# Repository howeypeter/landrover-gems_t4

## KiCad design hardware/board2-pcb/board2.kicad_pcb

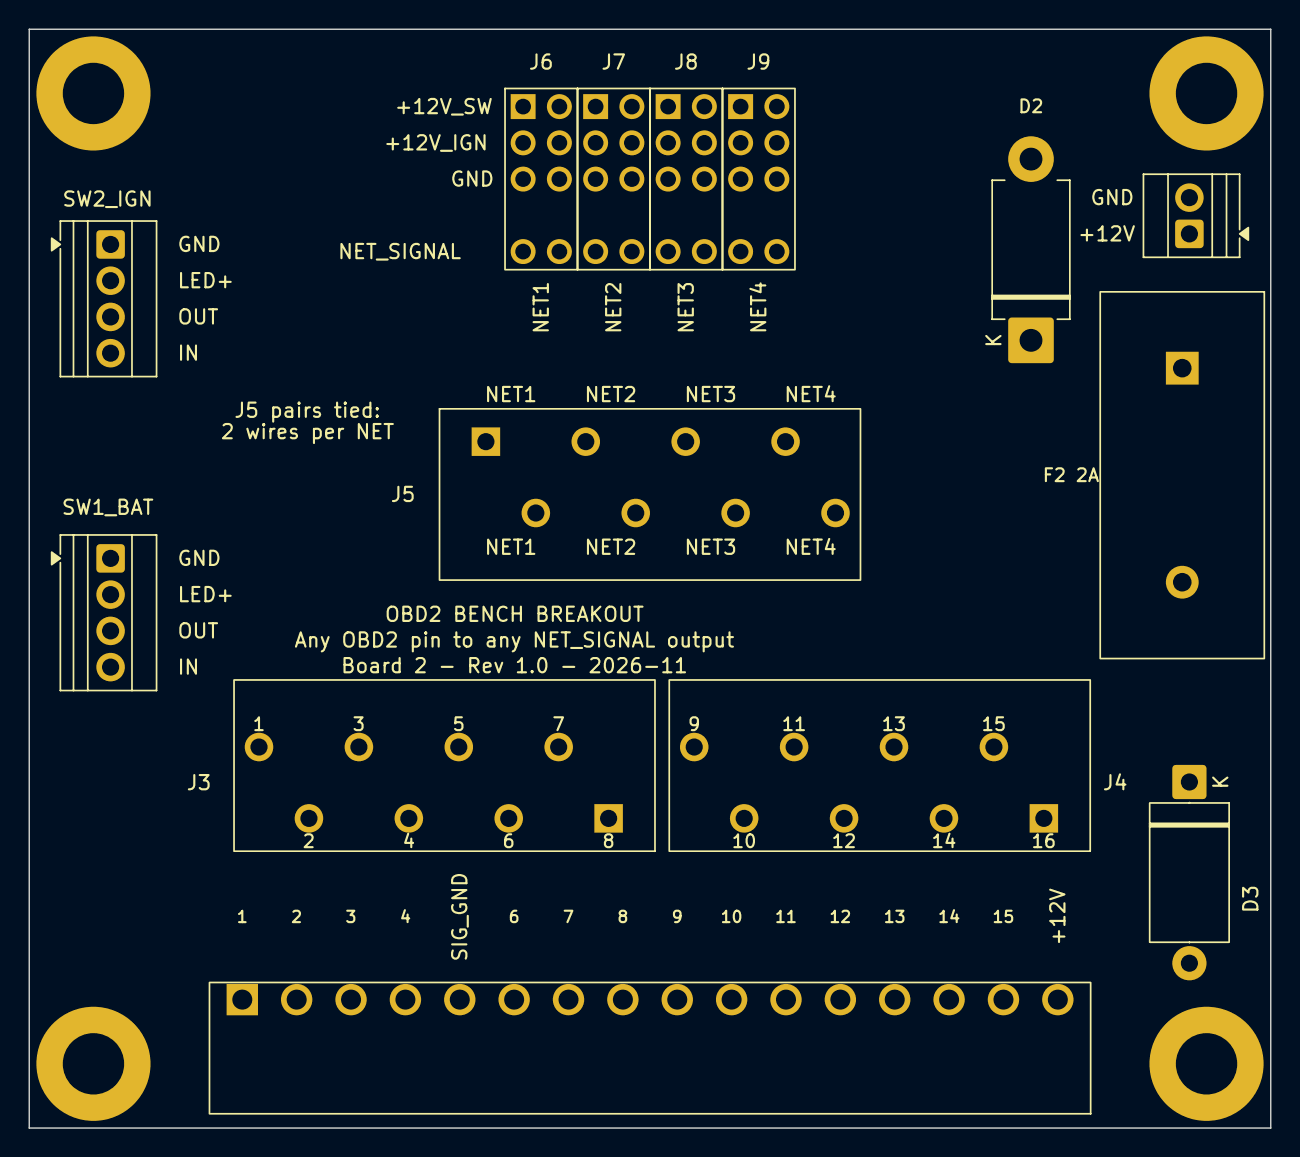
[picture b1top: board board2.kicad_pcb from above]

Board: 2 copper layers, 87.0 x 77.0 mm, 18 parts (0 on the bottom side), 24 nets, no tracks yet.

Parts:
D2: D2; D_DO-201AD_P12.70mm_Horizontal
D3: D3; D_DO-27_P12.70mm_Horizontal
F2: F2; Fuseholder_2pin_5x20_P15mm
H: MountingHole_4.3mm_M4_Pad
H#2, H#3, H#4: MountingHole_4.3mm_M4_Pad
J1: J1; TerminalBlock_Xinya_XY308-2.54-2P_1x02_P2.54mm_Horizontal
J2: J2; SameSky_TBP02R1-381-16BE_1x16_P3.81mm_RA_PinsReversed
J3: J3; SameSky_TBL002A-350-08_1x08_P3.50mm_45deg
J4: J4; SameSky_TBL002A-350-08_1x08_P3.50mm_45deg
J5: J5; SameSky_TBL002A-350-08_1x08_P3.50mm_45deg
J6: J6; Harwin_M20-9980546_2x05_P2.54mm_Vertical_KeyRowRemoved
J7: J7; Harwin_M20-9980546_2x05_P2.54mm_Vertical_KeyRowRemoved
J8: J8; Harwin_M20-9980546_2x05_P2.54mm_Vertical_KeyRowRemoved
J9: J9; Harwin_M20-9980546_2x05_P2.54mm_Vertical_KeyRowRemoved
SW1: SW1; TerminalBlock_Xinya_XY308-2.54-4P_1x04_P2.54mm_Horizontal
SW2: SW2; TerminalBlock_Xinya_XY308-2.54-4P_1x04_P2.54mm_Horizontal

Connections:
GND: D3.2, J1.2, J2.5, J3.4, J6.5, J6.6, J7.5, J7.6, J8.5, J8.6, J9.5, J9.6, SW1.1, SW2.1
IGN: J6.3, J6.4, J7.3, J7.4, J8.3, J8.4, J9.3, J9.4, SW2.2, SW2.3
NET1: J5.1, J5.2, J6.9, J6.10
NET2: J5.3, J5.4, J7.9, J7.10
NET3: J5.5, J5.6, J8.9, J8.10
NET4: J5.7, J5.8, J9.9, J9.10
OBD1: J2.1, J3.8
OBD2: J2.2, J3.7
OBD3: J2.3, J3.6
OBD4: J2.4, J3.5
OBD6: J2.6, J3.3
OBD7: J2.7, J3.2
OBD8: J2.8, J3.1
OBD9: J2.9, J4.8
OBD10: J2.10, J4.7
OBD11: J2.11, J4.6
OBD12: J2.12, J4.5
OBD13: J2.13, J4.4
OBD14: J2.14, J4.3
OBD15: J2.15, J4.2
V12S: J2.16, J4.1, J6.1, J6.2, J7.1, J7.2, J8.1, J8.2, J9.1, J9.2, SW1.2, SW1.3, SW2.4
VD: D2.1, F2.1
VF: D3.1, F2.2, SW1.4
VJ2: D2.2, J1.1

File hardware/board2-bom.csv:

Reference,Manufacturer,Manufacturer Part Number,Description,Quantity,Status
D2,Diodes Inc./onsemi/any,SB540,5A 40V Schottky through-hole DO-201AD (replaces SS54 and 1N5822),1,chosen
D3,Littelfuse/any,1.5KE24A,1500W 24V unidirectional TVS DO-27 axial,1,on hand
J3,Same Sky,TBP02R1-381-16BE,16-pos 3.81mm right-angle (horizontal) pluggable header; standard blue housing (replaces Amphenol Anytek OQ1632510000G),1,confirmed
J3 mate,Same Sky,TBP02P1-381-16BE,16-pos 3.81mm pluggable screw-terminal plug (180deg wire entry; Board 1 pigtail lands here); mates TBP02R1-381 series per Same Sky mating guide,1,confirmed
J7/J6,Same Sky,TBL002A-350-08GR-2OR,8-pos 3.5mm 45deg push-button terminal block (2 for J7 + 1 for J6),3,confirmed
J4,Harwin,M20-9980546,2x5 (10-pos) 2.54mm vertical pin header; 4 side by side = 5 rows x 8 columns; pull the 2 key-row pins (row 4) from each header (Mouser listing not yet confirmed),4,chosen - verify before ordering
J4 mate (1 column),Harwin,M20-1060500,1x5 female crimp housing 2.54mm (key plug in slot 4); Mouser number not confirmed,as needed,verify part number
J4 mate (2 columns),Harwin,M20-1070500,2x5 (5+5) female crimp housing 2.54mm; Mouser number not confirmed,as needed,verify part number
J4 key plug,Harwin,M20-003,Polarizing key plug for M20 housings (goes in slot 4 of each cable housing),as needed,verify part number
J4 crimp contacts,Harwin,M20-1160042 / M20-1160046 / M20-1180042 / M20-1180046,Female crimp contacts for the M20 housings 22-30 AWG (or pre-crimped leads - fit in the Harwin housing unconfirmed),as needed,verify part number
J2,XINLAIYA,XY308-2.54-2P,2-pos 2.54 mm screw terminal (LCSC C557685); 12V DC input,1,chosen
SW1/SW2,XINLAIYA,XY308-2.54-4P,4-pos 2.54 mm screw terminal (LCSC C915913); one per switch,2,chosen

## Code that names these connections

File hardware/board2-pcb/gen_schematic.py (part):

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place(DIODE, "D2", "SB540", FP_D2, 20, 21, {"2": "VJ2", "1": "VD"}, "Reverse-polarity Schottky 5A/40V; cathode (band) toward F2")
place(FUSE, "F2", "2 A", FP_F2, 30, 21, {"1": "VD", "2": "VF"}, "2 A fuse + holder (OPEN)")
place(C1x04, "SW1", "4-pin screw terminal", FP_TB4, 42, 21,
      {"1": "GND", "2": "V12S", "3": "V12S", "4": "VF"}, "4-pin screw terminal to off-board illuminated switch (general power); pin 1 GND, pin 4 input (matches Board 1 convention)")
place(C1x04, "SW2", "4-pin screw terminal", FP_TB4, 62, 21,
      {"1": "GND", "2": "IGN", "3": "IGN", "4": "V12S"}, "4-pin screw terminal to off-board illuminated switch (shared 12V_IGN); pin 1 GND, pin 4 input (matches Board 1 convention)")
place(TVS, "D3", "1.5KE24A", FP_D3, 84, 21, {"1": "VF", "2": "GND"}, "TVS 1500W 24V unidirectional, DO-27; cathode (band) to VF (F2 out / SW1 in); 1.0 mm leads, 1.3 mm holes")

# ---- J2 / J3/J4 (fixed 1:1) ----
text("OBD2 INPUT (fixed 1:1):  J2 pin n  =  J3/J4 pin n   (pin 5 = GND, pin 16 = V12S)", 4, 36)
def obd(n):
    return "GND" if n == 5 else ("V12S" if n == 16 else f"OBD{n}")
place(C1x16, "J2", "TBP02R1-381-16BE (16-pos 3.81)", FP_J3, 8, 52, {str(n): obd(n) for n in range(1, 17)}, "From Board 1 OBD2 pigtail (male plug)")
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      {"1": "NET1", "2": "NET1", "3": "NET2", "4": "NET2", "5": "NET3", "6": "NET3", "7": "NET4", "8": "NET4"},
      "Pin pairs 1-2 = NET1, 3-4 = NET2, 5-6 = NET3, 7-8 = NET4 (reassigned 2026-11-14 to match the J5 silk; J6 at the -x end faces NET1, left to right from the front)")

# ---- J6-J9 outputs: 2x4 grid; pins 1 BAT, 2 NET, 3 IGN, 4 GND ----
text("J6-J9 OUTPUT GRID (4 x Harwin M20-9980546 2x5, 5 rows x 8 columns, 2.54 mm):  rows 1-5 = V12S, IGN, GND, key (pins pulled), NET;  columns = NET1a NET1b NET2a NET2b NET3a NET3b NET4a NET4b", 4, 90)
# Four Harwin M20-9980546 2x5 headers side by side = the 5-row x 8-column grid; header i holds columns 2i+1 (odd pins) and 2i+2 (even pins).
# Pins 1,2 = row 1 V12S; 3,4 = row 2 IGN; 5,6 = row 3 GND; 7,8 = row 4 KEY (pins pulled from the header, no holes); 9,10 = row 5 NETi.
for i in range(4):
    ref = f"J{6 + i}"
    place(C2x05, ref, "M20-9980546", FP_J4, 10 + 24 * i, 96,
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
